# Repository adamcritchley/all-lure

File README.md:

# Disclaimer
This board is still a prototype and is not functional. I was not able to fabricate it with working mSATA or mPCIe. I attempted to fabricate it with JLCPCB using both JLC041611-7628 and JLC041611-3313 impedance control. The presence detect for mSATA was pulled low however the MinnowBoard would not communicate with the mSATA card. I've decided not to continue troubleshooting this board and instead leave it as a learning experience in high-speed board design.

See [CM4-NAS-MiniPCIE](https://github.com/dumtux/CM4-NAS-MiniPCIE) as an example high-speed board designed for JLCPCB's JLC041611-7628 impedance control

# All-lure (GPIO, XDP, mPCIe, mSATA expansion for MinnowBoard)
All-lure is a custom "lure" expansion board for MinnowBoard Single Board Computers (SBC). The official hardware designs for MinnowBoard and the lures can be found at [MinnowBoards official GitHub](https://github.com/MinnowBoard-org/design-files). However, each board only exposes a single capability through the HSE (i.e. mSATA or mPCIe), instead I wanted a single board that combined as much of the lures capabilities into a single lure.

# Fabrication
This board does not work, please do not fabricate it. Currently it's designed for fabrication with JLCPCB using 1oz inner and outer copper weight and the standard JLC041611-7628 impedance control.

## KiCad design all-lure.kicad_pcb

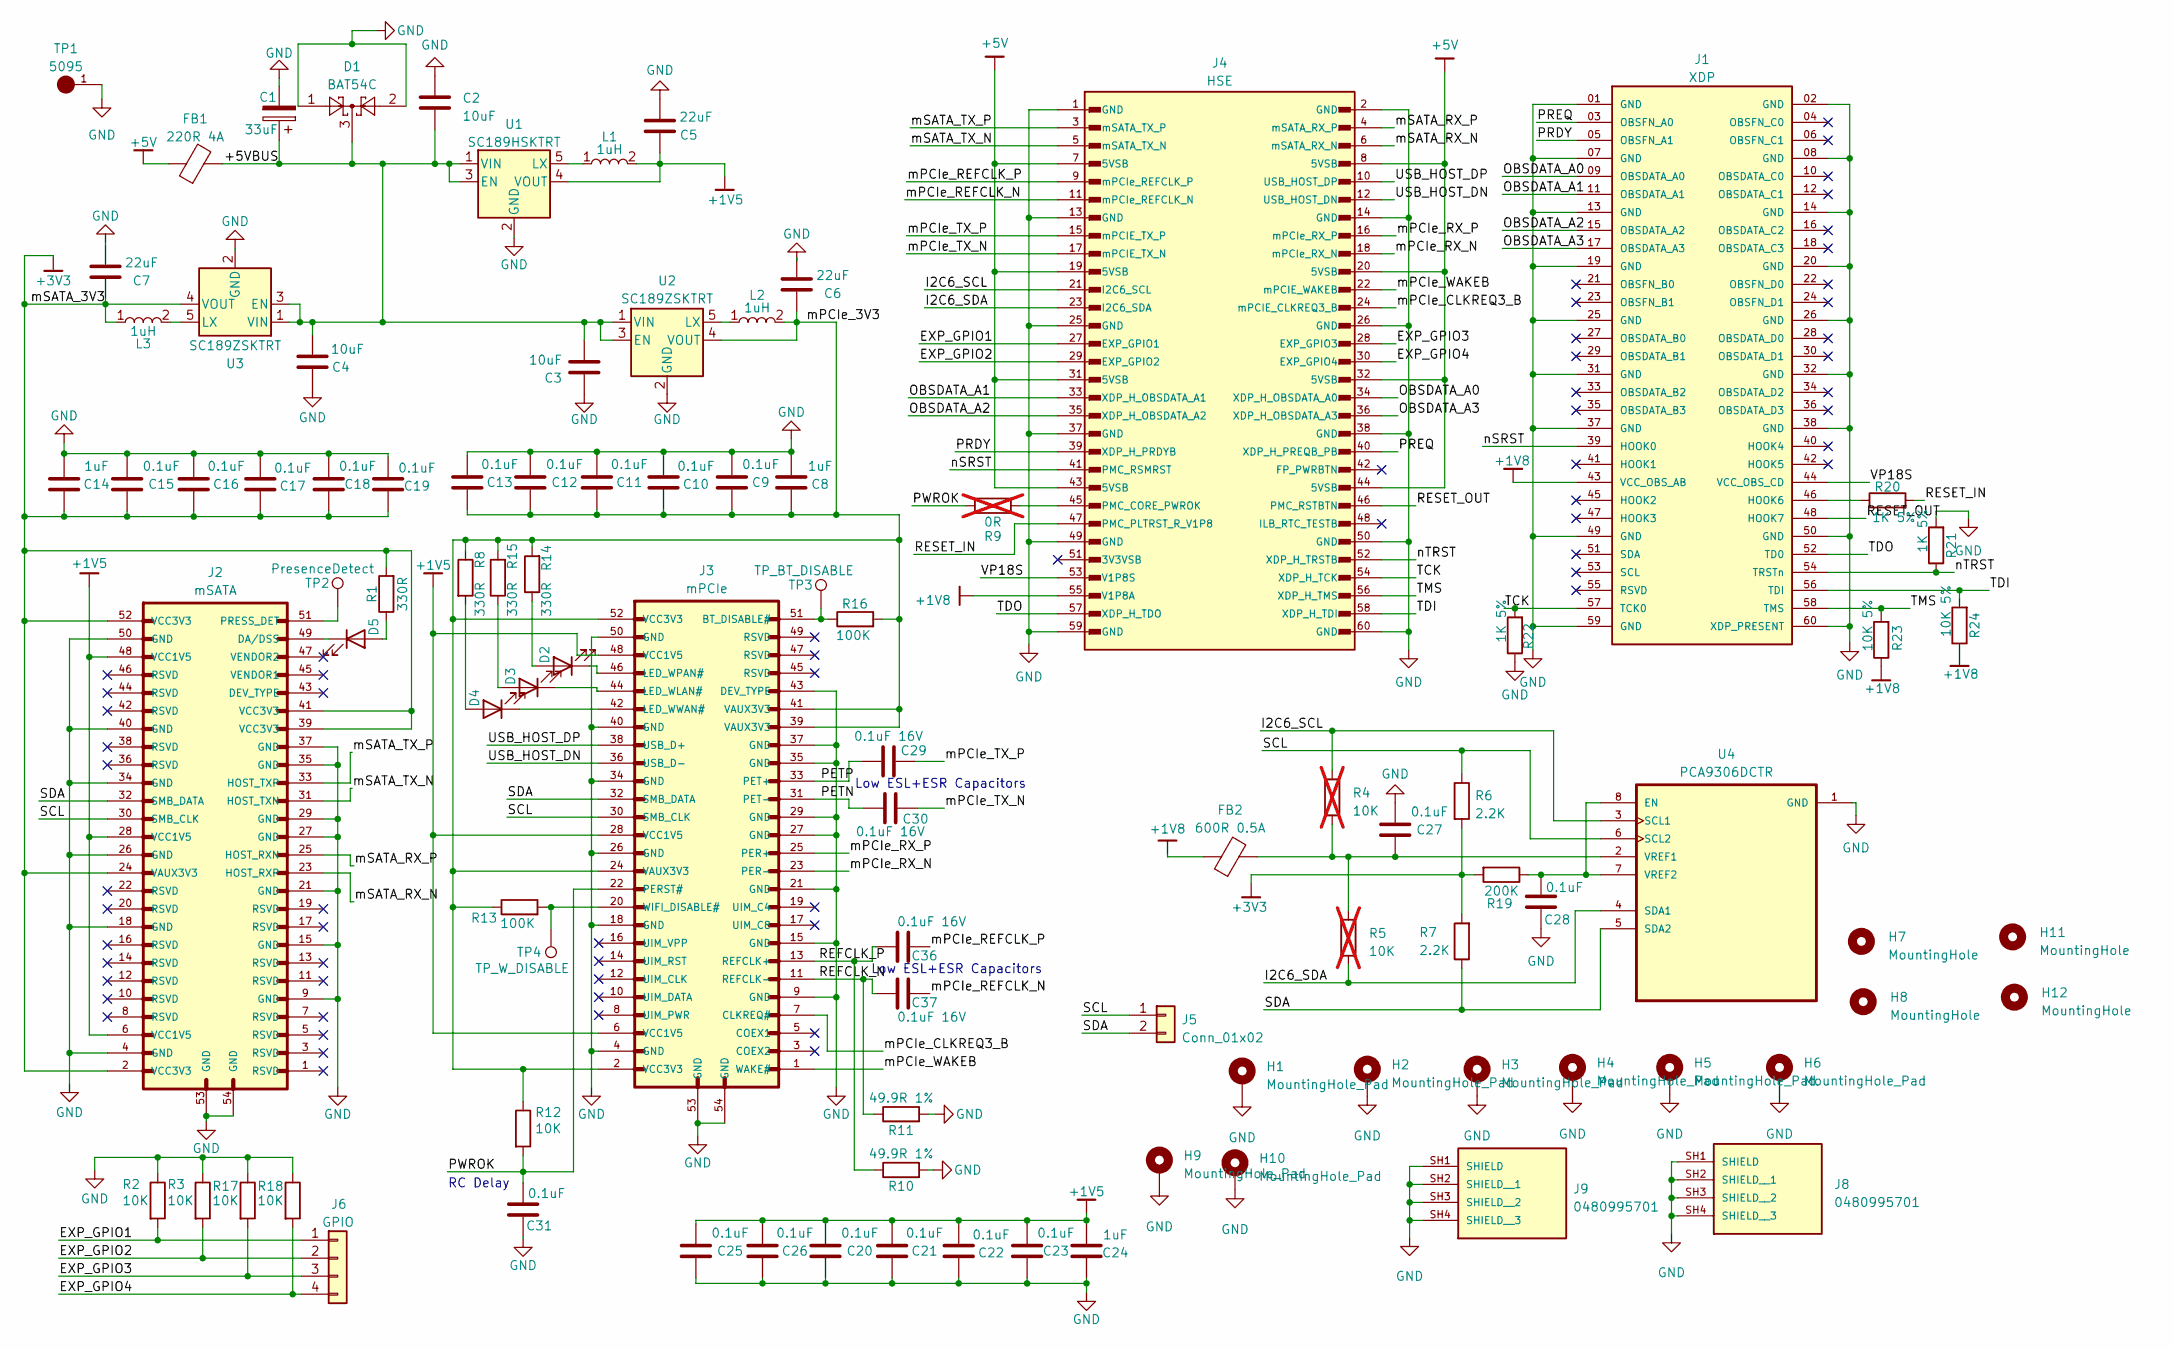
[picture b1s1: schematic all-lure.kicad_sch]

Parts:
C1: 33uF; CP_EIA-3216-18_Kemet-A_Pad1.58x1.35mm_HandSolder; MPN TPSA336K010R0700
C2, C3, C4: 10uF; C_0603_1608Metric_Pad1.08x0.95mm_HandSolder; MPN CL10A106KQ8NNNC
C5, C6, C7: 22uF; C_0603_1608Metric_Pad1.08x0.95mm_HandSolder; MPN CL10A226MP8NUNE
C8, C14, C24: 1uF; C_0603_1608Metric_Pad1.08x0.95mm_HandSolder; MPN CL10B105KO8NNNC
C9, C10, C11, C12, C13, C15, C16, C17, C18, C19, C20, C21, C22, C23, C25, C26, C27, C28, C31: 0.1uF; C_0603_1608Metric_Pad1.08x0.95mm_HandSolder; MPN CL10B104KO8NNNC
C29, C30, C36, C37: 0.1uF 16V; C_0402_1005Metric_Pad0.74x0.62mm_HandSolder; MPN NMC0402X7R104K25TRPF
D1: BAT54C; SOT-23; MPN BAT54CLT3G
D2, D3, D4, D5: LED; LTST-S270TGKT-HandSolder; MPN LTST-C190GKT
FB1: 220R 4A; D_1206_3216Metric_Pad1.42x1.75mm_HandSolder; MPN LCMGA321616T221NG
FB2: 600R 0.5A; D_0603_1608Metric_Pad1.05x0.95mm_HandSolder; MPN MMZ1608B601CTAH0
H1, H2, H9, H10: MountingHole_Pad; MountingHole_4.3mm_M4_Pad
H3, H4, H5, H6: MountingHole_Pad; MountingHole_3.5mm_Pad
H7, H8: MountingHole; MountingHole_6.4mm_M6_DIN965
H11, H12: MountingHole; MountingHole_3.2mm_M3_DIN965
J1: XDP; SAMTEC_BSH-030-01-X-D; PARTREV D
J2: mSATA; MOLEX_67910-5700; MPN 67910-5700
J3: mPCIe; MOLEX_67910-5700; MPN 67910-5700
J4: HSE; TE_3-5177986-2; PARTREV 9-06
J5: Conn_01x02; PinHeader_1x02_P2.54mm_Vertical
J6: GPIO; PinHeader_1x04_P2.54mm_Vertical
J8, J9: 0480995701; MOLEX_0480995701; PARTREV G
L1, L2, L3: 1uH; INDC2016X100N; MPN MAKK2016T1R0M
R1, R8, R14, R15: 330R; R_0603_1608Metric_Pad0.98x0.95mm_HandSolder; MPN SR0603FR-7T330RL
R2, R3, R17, R18: 10K; R_1206_3216Metric_Pad1.30x1.75mm_HandSolder; MPN RC1206FR-0710KL
R4, R5: 10K; R_0603_1608Metric_Pad0.98x0.95mm_HandSolder; not fitted
R6, R7: 2.2K; R_0603_1608Metric_Pad0.98x0.95mm_HandSolder; MPN SR0603FR-7T2K2L
R9: 0R; R_0603_1608Metric_Pad0.98x0.95mm_HandSolder; not fitted
R10, R11: 49.9R 1%; R_0402_1005Metric_Pad0.72x0.64mm_HandSolder; MPN RC0402FR-0749R9L
R12: 10K; R_0603_1608Metric_Pad0.98x0.95mm_HandSolder; MPN SR0603FR-7T10KL
R13, R16: 100K; R_0603_1608Metric_Pad0.98x0.95mm_HandSolder; MPN SR0603FR-7T100KL
R19: 200K; R_0603_1608Metric_Pad0.98x0.95mm_HandSolder; MPN RC0603FR-13200KL
R20, R21, R22: 1K 5%; R_0603_1608Metric_Pad0.98x0.95mm_HandSolder; MPN RC0603JR-131KL
R23, R24: 10K 5%; R_0603_1608Metric_Pad0.98x0.95mm_HandSolder; MPN RC1206FR-0710KL
TP1: 5095; KEYSTONE_5095; MPN 5095
TP2: PresenceDetect; TestPoint_Pad_D1.5mm
TP3: TP_BT_DISABLE; TestPoint_Pad_D1.5mm
TP4: TP_W_DISABLE; TestPoint_Pad_D1.5mm
U1: SC189HSKTRT; SOT-23-5; MPN SC189HSKTRT
U2, U3: SC189ZSKTRT; SOT-23-5; MPN SC189ZSKTRT
U4: PCA9306DCTR; SOP65P400X130-8N; MPN PCA9306DCTR; DigiKey_Part_Number 296-18509-2-ND

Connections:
+1V5: C5.1, C20.2, C21.2, C22.2, C23.2, C24.2, C25.2, C26.2, J2.6 (VCC1V5), J2.28 (VCC1V5), J2.48 (VCC1V5), J3.6 (VCC1V5), J3.28 (VCC1V5), J3.48 (VCC1V5), L1.2, U1.4 (VOUT)
+1V8: FB2.1, J1.43 (VCC_OBS_AB), J4.55 (V1P8A), R23.1, R24.1
+3V3: C7.1, C14.1, C15.1, C16.1, C17.1, C18.1, C19.1, J2.2 (VCC3V3), J2.24 (VAUX3V3), J2.39 (VCC3V3), J2.41 (VCC3V3), J2.52 (VCC3V3), L3.1, R1.2, R6.2, R7.2, R19.2, U3.4 (VOUT)
+5V: FB1.1, J4.7 (5VSB), J4.8 (5VSB), J4.19 (5VSB), J4.20 (5VSB), J4.31 (5VSB), J4.32 (5VSB), J4.43 (5VSB), J4.44 (5VSB)
/+5VBUS: C1.1, C2.1, C3.1, C4.1, D1.3, FB1.2, U1.1 (VIN), U1.3 (EN), U2.1 (VIN), U2.3 (EN), U3.1 (VIN), U3.3 (EN)
/EXP_GPIO1: J4.27 (EXP_GPIO1), J6.1, R2.2
/EXP_GPIO2: J4.29 (EXP_GPIO2), J6.2, R3.2
/EXP_GPIO3: J4.28 (EXP_GPIO3), J6.3, R17.2
/EXP_GPIO4: J4.30 (EXP_GPIO4), J6.4, R18.2
/I2C6_SCL: J4.21 (I2C6_SCL), R4.1, U4.3 (SCL1)
/I2C6_SDA: J4.23 (I2C6_SDA), R5.2, U4.4 (SDA1)
/OBSDATA_A0: J1.09 (OBSDATA_A0), J4.34 (XDP_H_OBSDATA_A0)
/OBSDATA_A1: J1.11 (OBSDATA_A1), J4.33 (XDP_H_OBSDATA_A1)
/OBSDATA_A2: J1.15 (OBSDATA_A2), J4.35 (XDP_H_OBSDATA_A2)
/OBSDATA_A3: J1.17 (OBSDATA_A3), J4.36 (XDP_H_OBSDATA_A3)
/PETN: C30.1, J3.31 (PET-)
/PETP: C29.1, J3.33 (PET+)
/PRDY: J1.05 (OBSFN_A1), J4.39 (XDP_H_PRDYB)
/PREQ: J1.03 (OBSFN_A0), J4.40 (XDP_H_PREQB_PB)
/PWROK: C31.2, J3.22 (PERST#), R9.2, R12.2
/RESET_IN: J4.47 (PMC_PLTRST_R_V1P8), R20.2
/RESET_OUT: J1.48 (HOOK7), J4.46 (PMC_RSTBTN)
/SCL: J2.30 (SMB_CLK), J3.30 (SMB_CLK), J5.1, R6.1, U4.6 (SCL2)
/SDA: J2.32 (SMB_DATA), J3.32 (SMB_DATA), J5.2, R7.1, U4.5 (SDA2)
/TCK: J1.57 (TCK0), J4.54 (XDP_H_TCK), R22.2
/TDI: J1.56 (TDI), J4.58 (XDP_H_TDI), R24.2
/TDO: J1.52 (TD0), J4.57 (XDP_H_TDO)
/TMS: J1.58 (TMS), J4.56 (XDP_H_TMS), R23.2
/USB_HOST_DN: J3.36 (USB_D-), J4.12 (USB_HOST_DN)
/USB_HOST_DP: J3.38 (USB_D+), J4.10 (USB_HOST_DP)
/VP18S: J1.44 (VCC_OBS_CD), J4.53 (V1P8S)
/mPCIe_3V3: C6.1, C8.1, C9.1, C10.1, C11.1, C12.1, C13.1, J3.2 (VCC3V3), J3.24 (VAUX3V3), J3.39 (VAUX3V3), J3.41 (VAUX3V3), J3.52 (VCC3V3), L2.2, R8.1, R12.1, R13.1, R14.2, R15.2, R16.2, U2.4 (VOUT)
/mPCIe_CLKREQ3_B: J3.7 (CLKREQ#), J4.24 (mPCIE_CLKREQ3_B)
/mPCIe_RX_N: J3.23 (PER-), J4.18 (mPCIe_RX_N)
/mPCIe_RX_P: J3.25 (PER+), J4.16 (mPCIe_RX_P)
/mPCIe_TX_N: C30.2, J4.17 (mPCIE_TX_N)
/mPCIe_TX_P: C29.2, J4.15 (mPCIE_TX_P)
/mPCIe_WAKEB: J3.1 (WAKE#), J4.22 (mPCIE_WAKEB)
/mSATA_RX_N: J2.23 (HOST_RXP), J4.6 (mSATA_RX_N)
/mSATA_RX_P: J2.25 (HOST_RXN), J4.4 (mSATA_RX_P)
/mSATA_TX_N: J2.31 (HOST_TXN), J4.5 (mSATA_TX_N)
/mSATA_TX_P: J2.33 (HOST_TXP), J4.3 (mSATA_TX_P)
/nSRST: J1.39 (HOOK0), J4.41 (PMC_RSMRST)
/nTRST: J1.54 (TRSTn), J4.52 (XDP_H_TRSTB), R21.1
GND: C1.2, C2.2, C3.2, C4.2, C5.2, C6.2, C7.2, C8.2, C9.2, C10.2, C11.2, C12.2, C13.2, C14.2, C15.2, C16.2, C17.2, C18.2, C19.2, C20.1, C21.1, C22.1, C23.1, C24.1, C25.1, C26.1, C27.2, C28.1, C31.1, D1.1, D1.2, H1.1, H2.1, H3.1, H4.1, H5.1, H6.1, H9.1, H10.1, J1.01 (GND), J1.02 (GND), J1.07 (GND), J1.08 (GND), J1.13 (GND), J1.14 (GND), J1.19 (GND), J1.20 (GND), J1.25 (GND), J1.26 (GND), J1.31 (GND), J1.32 (GND), J1.37 (GND), J1.38 (GND), J1.49 (GND), J1.50 (GND), J1.59 (GND), J1.60 (XDP_PRESENT), J2.4 (GND), J2.9 (GND), J2.15 (GND), J2.18 (GND), J2.21 (GND), J2.26 (GND), J2.27 (GND), J2.29 (GND), J2.34 (GND), J2.35 (GND), J2.37 (GND), J2.40 (GND), J2.50 (GND), J2.53 (GND), J2.54 (GND), J3.4 (GND), J3.9 (GND), J3.15 (GND), J3.18 (GND), J3.21 (GND), J3.26 (GND), J3.27 (GND), J3.29 (GND), J3.34 (GND), J3.35 (GND), J3.37 (GND), J3.40 (GND), J3.43 (DEV_TYPE), J3.50 (GND), J3.53 (GND), J3.54 (GND), J4.1 (GND), J4.2 (GND), J4.13 (GND), J4.14 (GND), J4.25 (GND), J4.26 (GND), J4.37 (GND), J4.38 (GND), J4.49 (GND), J4.50 (GND), J4.59 (GND), J4.60 (GND), J8.SH1 (SHIELD), J8.SH2 (SHIELD__1), J8.SH3 (SHIELD__2), J8.SH4 (SHIELD__3), J9.SH1 (SHIELD), J9.SH2 (SHIELD__1), J9.SH3 (SHIELD__2), J9.SH4 (SHIELD__3), R2.1, R3.1, R10.2, R11.2, R17.1, R18.1, R21.2, R22.1, TP1.1, U1.2 (GND), U2.2 (GND), U3.2 (GND), U4.1 (GND)
unnamed: D2.2 (A), R14.1
unnamed: D2.1 (K), J3.46 (LED_WPAN#)
unnamed: D3.2 (A), R15.1
unnamed: D3.1 (K), J3.44 (LED_WLAN#)
unnamed: D4.2 (A), R8.2
unnamed: D4.1 (K), J3.42 (LED_WWAN#)
unnamed: D5.2 (A), R1.1
unnamed: D5.1 (K), J2.49 (DA/DSS)
unnamed: J1.46 (HOOK6), R20.1
unnamed: J2.51 (PRESS_DET), TP2.1
unnamed: J3.51 (BT_DISABLE#), R16.1, TP3.1
unnamed: J3.20 (WIFI_DISABLE#), R13.2, TP4.1
unnamed: J4.45 (PMC_CORE_PWROK), R9.1
unnamed: L1.1, U1.5 (LX)
unnamed: L2.1, U2.5 (LX)
unnamed: L3.2, U3.5 (LX)
unnamed: C28.2, R19.1, U4.7 (VREF2), U4.8 (EN)
unnamed: C27.1, FB2.2, R4.2, R5.1, U4.2 (VREF1)

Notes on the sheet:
Low ESL+ESR Capacitors
RC Delay

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
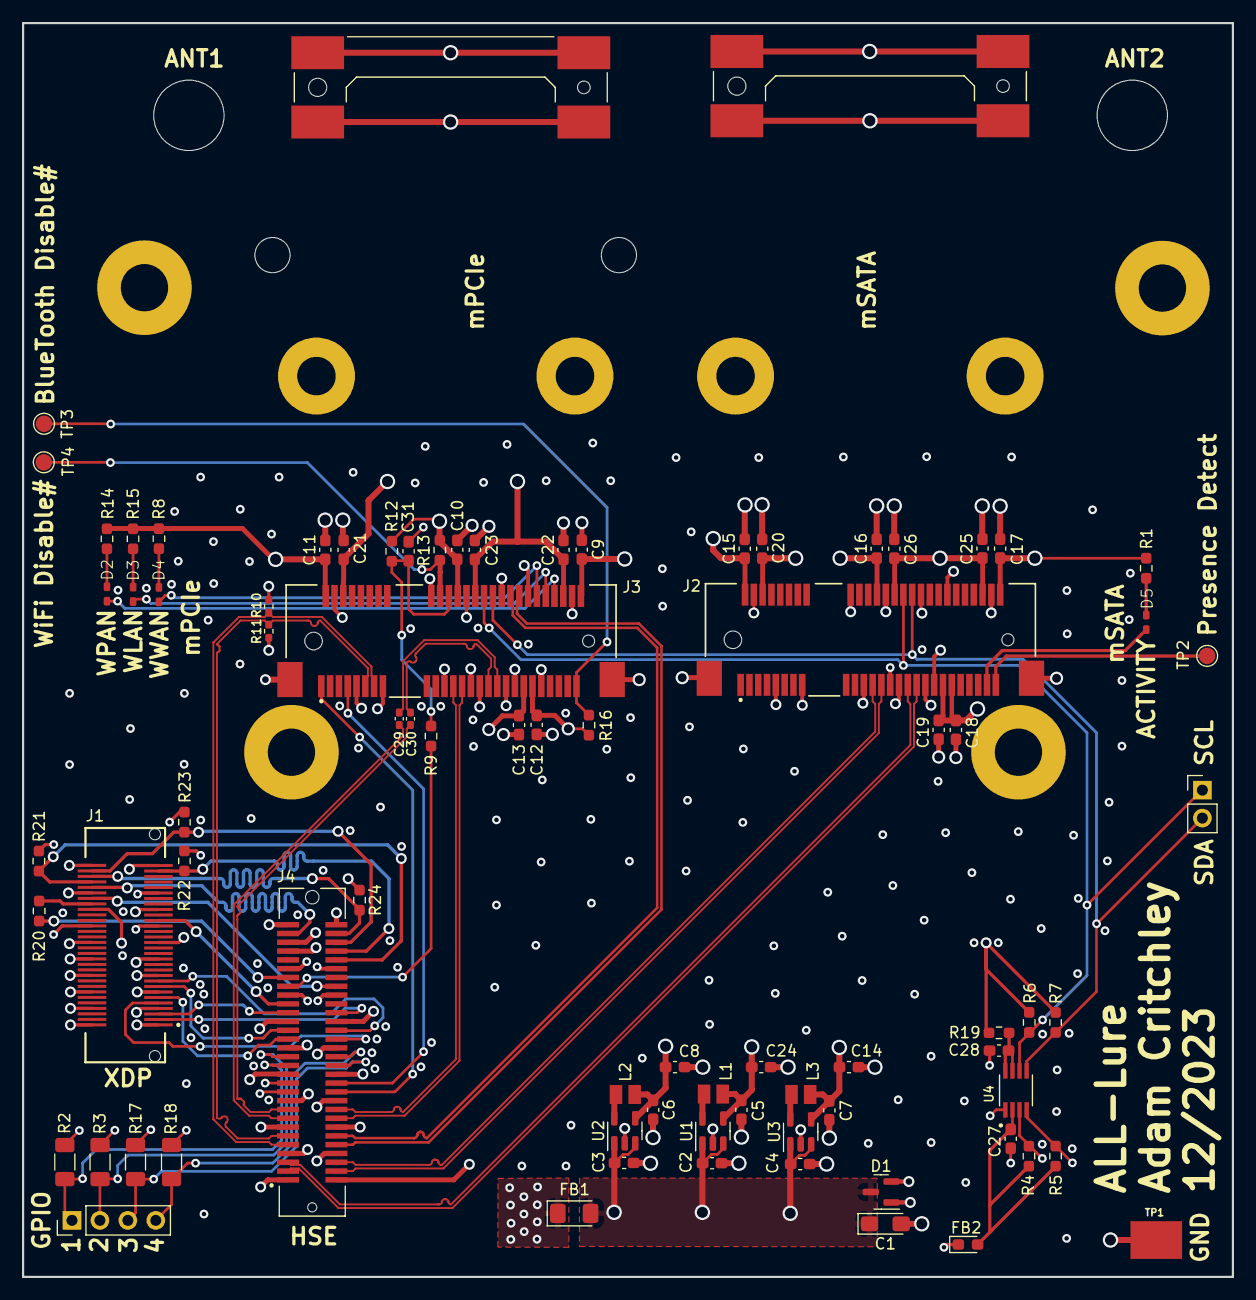
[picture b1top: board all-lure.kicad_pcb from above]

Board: 4 copper layers, 110.0 x 114.0 mm, 93 parts (0 on the bottom side), 65 nets.

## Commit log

2023-12-28 fact(pcb): change trace width for 3313 fabrication. meander jtag traces. fix broken ground plane under pci ref clock.
2024-01-13 feat(pcb): update with latest attempt at mSATA and mPCIE
